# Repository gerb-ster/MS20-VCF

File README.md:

# Korg MS20 VCF

A(nother) eurorack adaptation of this classic Korg VCF from the MS20. 

## Status: Finished

- done: first schematic & board design
- done: breadboard and test
- done: design frontpanel
- done: order PCB and build prototype

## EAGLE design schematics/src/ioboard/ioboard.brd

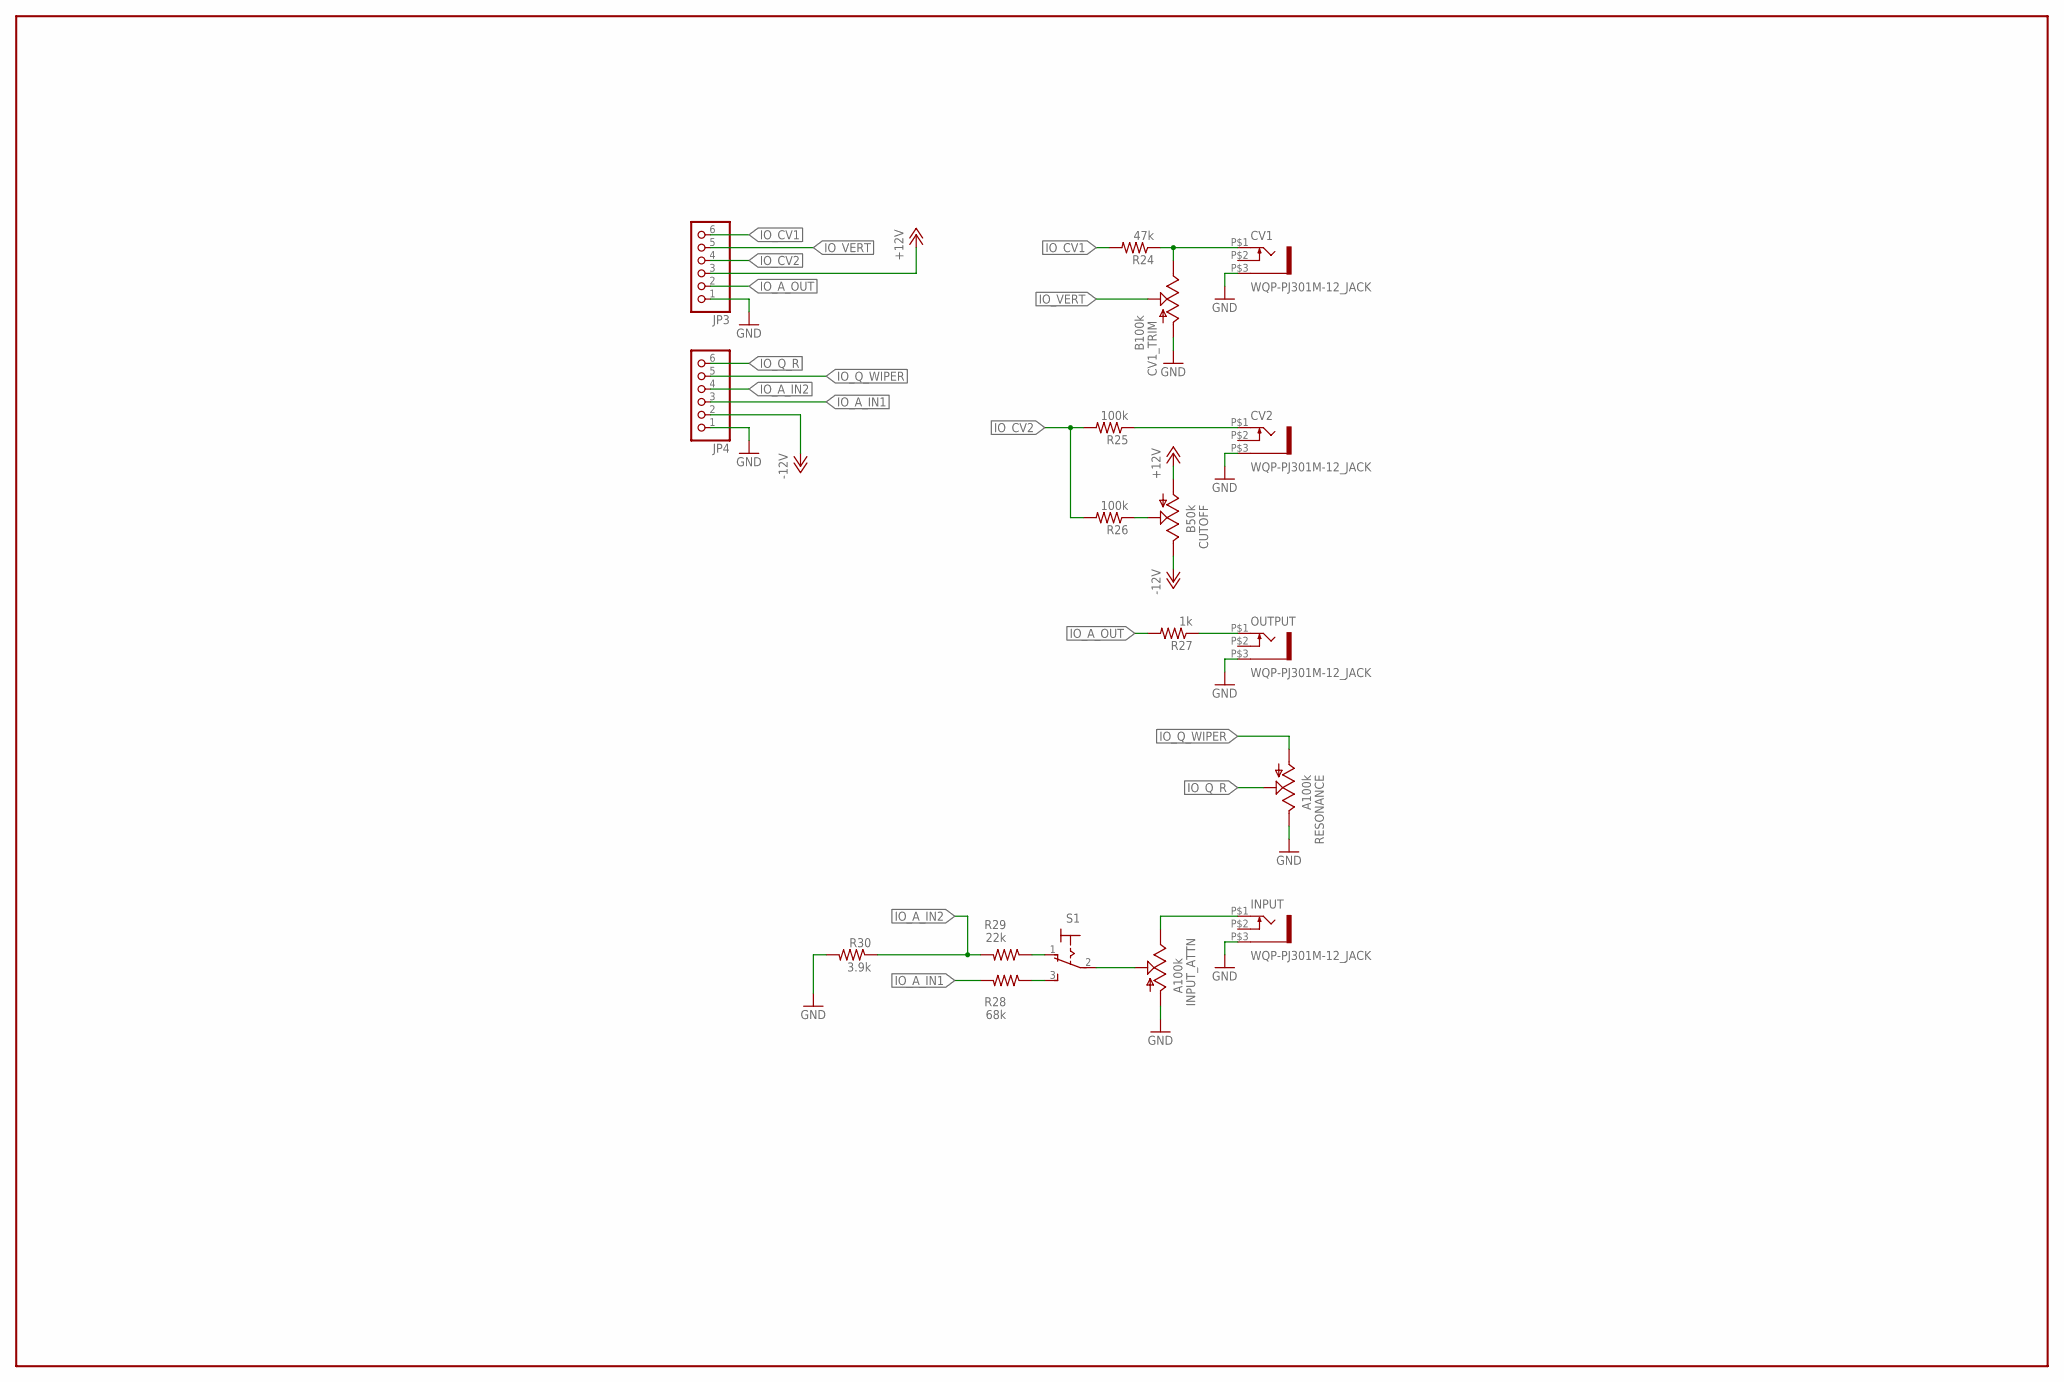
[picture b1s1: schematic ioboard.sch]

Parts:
CUTOFF: B50k; EVUF
CV1, CV2: WQP-PJ301M-12_JACK
CV1_TRIM: B100k; EVUF
INPUT: WQP-PJ301M-12_JACK
INPUT_ATTN: A100k; EVUF
JP3, JP4: PINHD-1X6; 1X06
OUTPUT: WQP-PJ301M-12_JACK
R24: 47k; 0207/7
R25, R26: 100k; 0207/7
R27: 1k; 0207/7
R28: 68k; 0207/7
R29: 22k; 0207/7
R30: 3.9k; 0207/7
RESONANCE: A100k; EVUF
S1: M9040P

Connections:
+12V: CUTOFF.1 (A), JP3.3
-12V: CUTOFF.3 (E), JP4.2
GND: CV1.P$3 (1), CV1_TRIM.1 (A), CV2.P$3 (1), INPUT.P$3 (1), INPUT_ATTN.1 (A), JP3.1, JP4.1, OUTPUT.P$3 (1), R30.2, RESONANCE.3 (E)
IO_A_IN1: JP4.3, R28.2
IO_A_IN2: JP4.4, R29.2, R30.1
IO_A_OUT: JP3.2, R27.2
IO_CV1: JP3.6, R24.2
IO_CV2: JP3.4, R25.2, R26.2
IO_Q_R: JP4.6, RESONANCE.2 (S)
IO_Q_WIPER: JP4.5, RESONANCE.1 (A)
IO_VERT: CV1_TRIM.2 (S), JP3.5
unnamed: CV2.P$1 (2), R25.1
unnamed: INPUT_ATTN.2 (S), S1.2
unnamed: CV1.P$1 (2), CV1_TRIM.3 (E), R24.1
unnamed: OUTPUT.P$1 (2), R27.1
unnamed: CUTOFF.2 (S), R26.1
unnamed: R29.1, S1.1 (O)
unnamed: R28.1, S1.3 (S)
unnamed: INPUT.P$1 (2), INPUT_ATTN.3 (E)

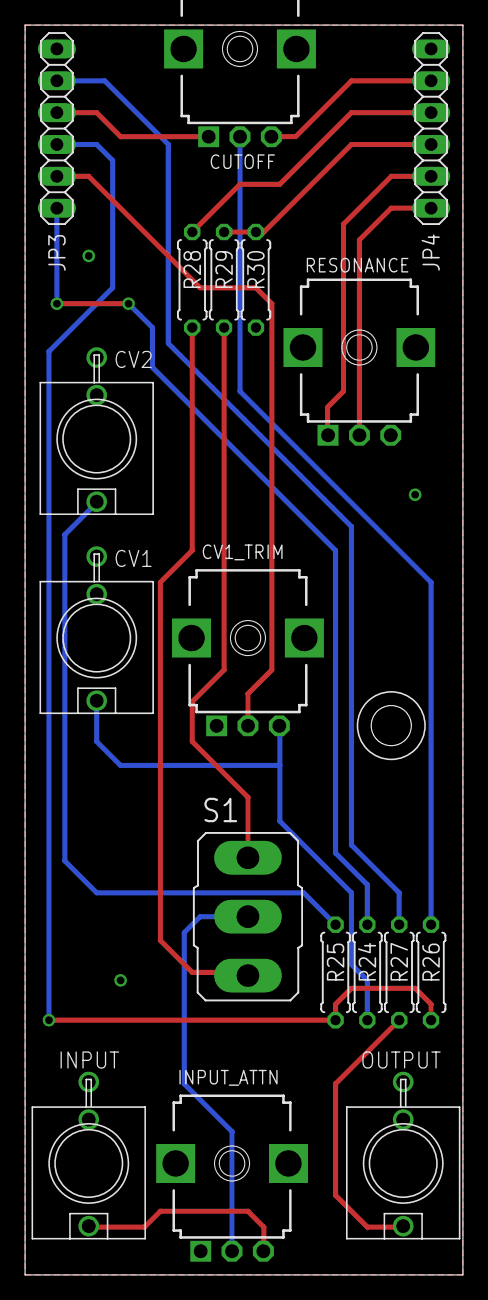
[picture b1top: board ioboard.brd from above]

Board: 2 copper layers, 34.9 x 99.7 mm, 18 parts (0 on the bottom side), 19 nets.

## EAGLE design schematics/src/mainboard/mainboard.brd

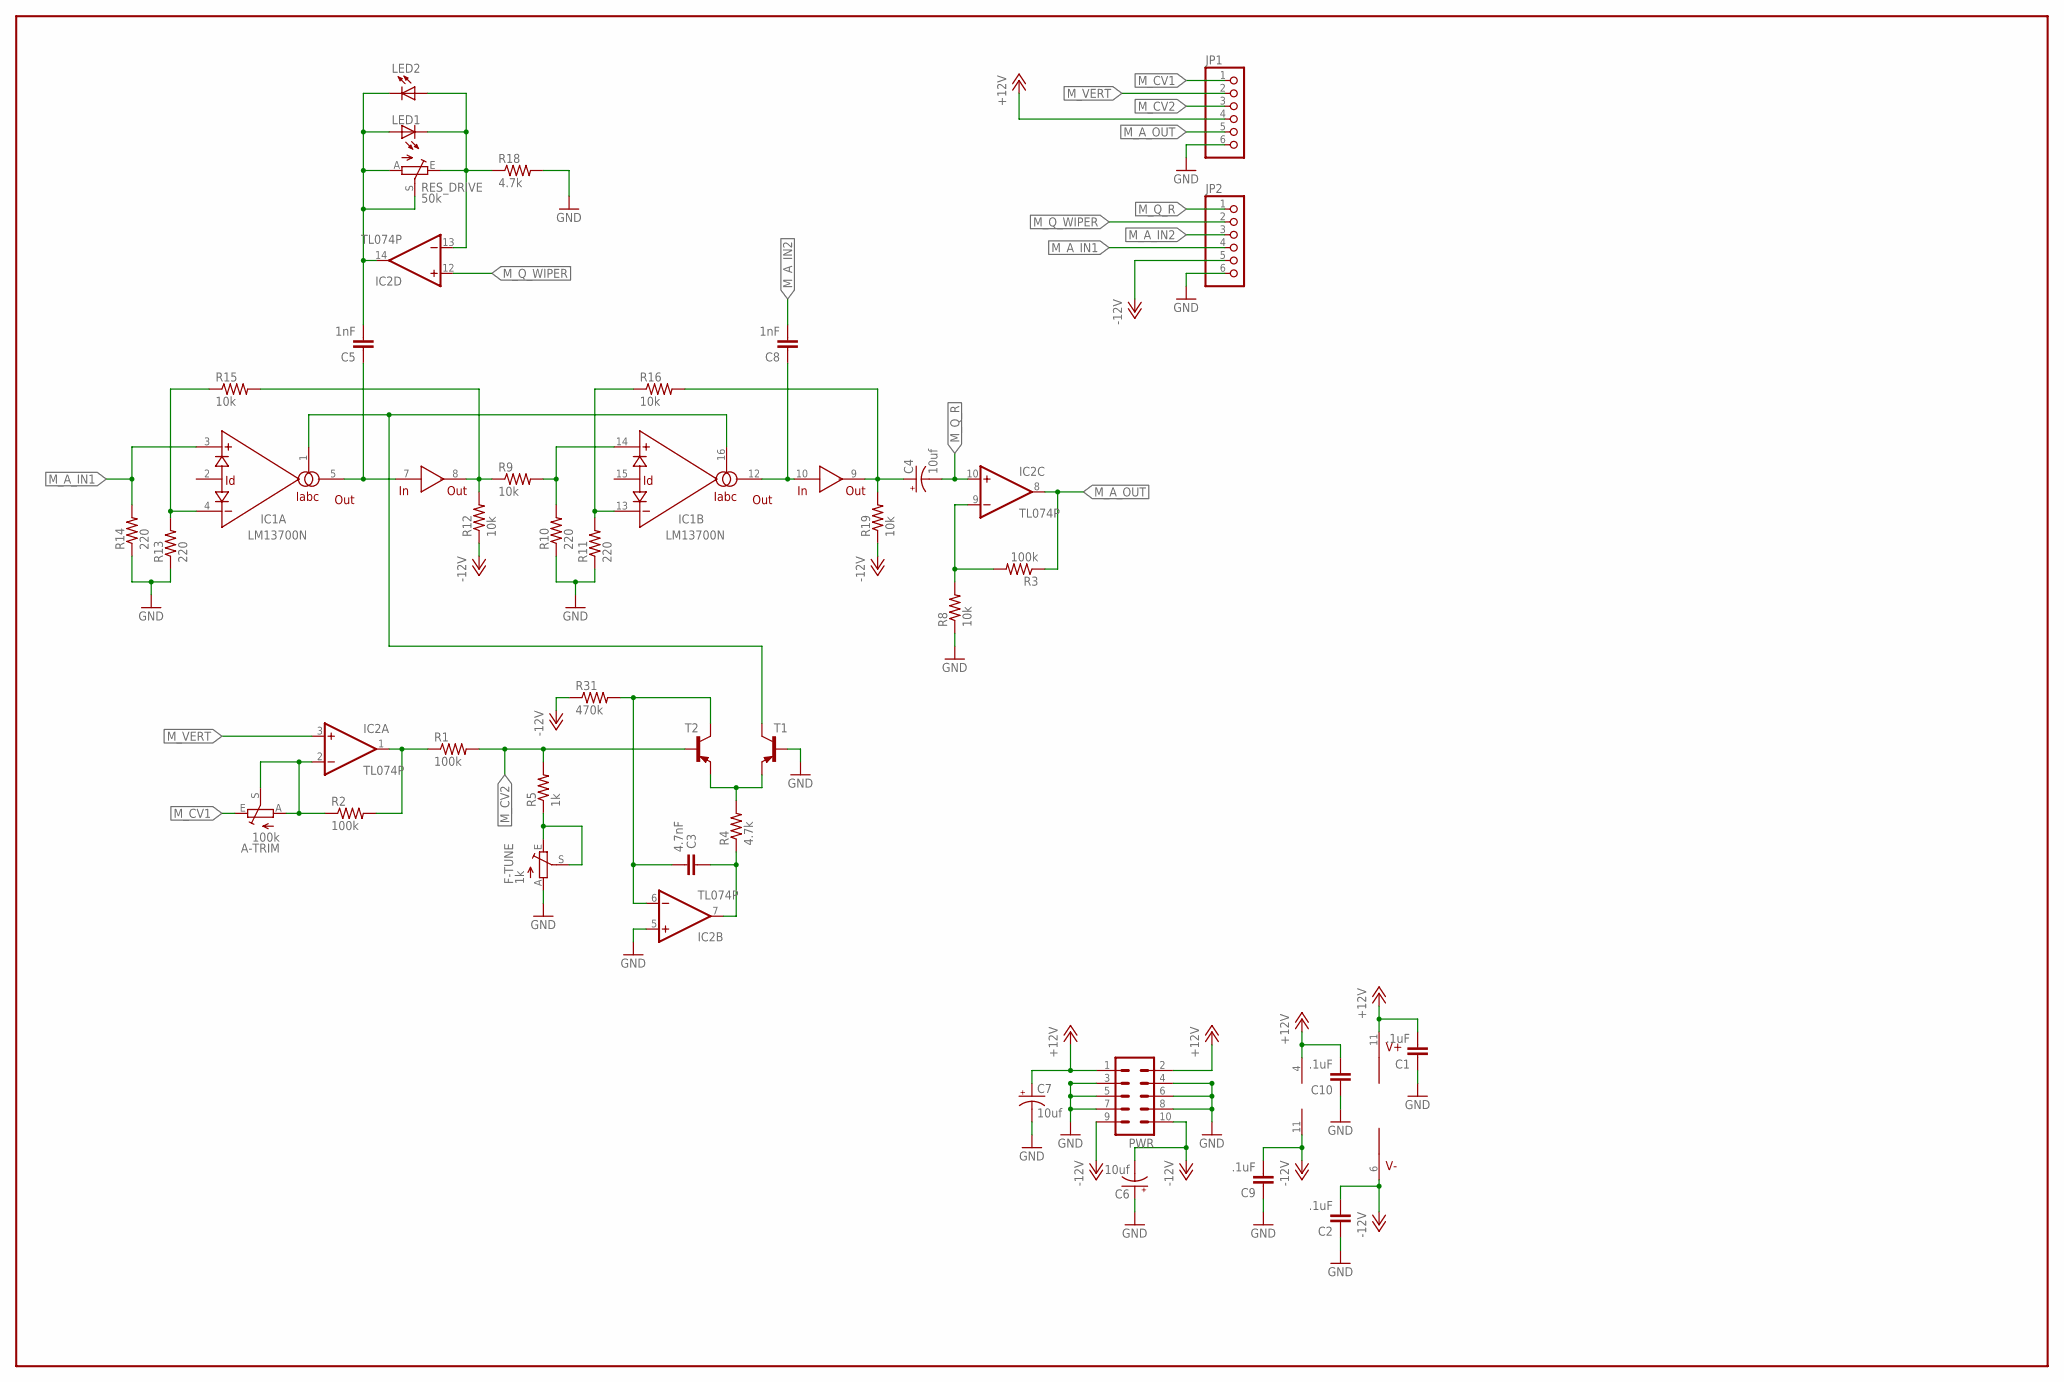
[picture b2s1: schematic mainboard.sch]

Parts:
A-TRIM: 100k; S64YW
C1, C2, C9, C10: .1uF; C050-024X044
C3: 4.7nF; C050-024X044
C4, C6, C7: 10uf; E2,5-5
C5, C8: 1nF; C050-025X075
F-TUNE: 1k; S64YW
IC1: LM13700N; DIL16
IC2: TL074P; DIL14
JP1, JP2: PINHD-1X6; 1X06
LED1, LED2: LED3MM
PWR: ML10
R1, R2, R3: 100k; 0207/7
R4, R18: 4.7k; 0207/7
R5: 1k; 0207/7
R8, R9, R12, R15, R16, R19: 10k; 0207/7
R10, R11, R13, R14: 220; 0207/7
R31: 470k; 0207/7
RES_DRIVE: 50k; S64YW
T1, T2: 2N3906-PNP-TO92-EBC; TO92-EBC

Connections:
+12V: C1.2, C7.+, C10.2, IC1.11 (V+), IC2.4 (V+), JP1.4, PWR.1, PWR.2
-12V: C2.2, C6.-, C9.2, IC1.6 (V-), IC2.11 (V-), JP2.5, PWR.9, PWR.10, R12.1, R19.1, R31.1
GND: C1.1, C2.1, C6.+, C7.-, C9.1, C10.1, F-TUNE.A, IC2.5 (+IN), JP1.6, JP2.6, PWR.3, PWR.4, PWR.5, PWR.6, PWR.7, PWR.8, R8.1, R10.1, R11.1, R13.1, R14.1, R18.2, T1.B
M_A_IN1: IC1.3 (+IN), JP2.4, R14.2
M_A_IN2: C8.2, JP2.3
M_A_OUT: IC2.8 (OUT), JP1.5, R3.1
M_CV1: A-TRIM.E, JP1.1
M_CV2: JP1.3, R1.2, R5.2, T2.B
M_Q_R: C4.-, IC2.10 (+IN), JP2.1
M_Q_WIPER: IC2.12 (+IN), JP2.2
M_VERT: IC2.3 (+IN), JP1.2
unnamed: IC2.1 (OUT), R1.1, R2.2
unnamed: R4.2, T1.E, T2.E
unnamed: A-TRIM.A, A-TRIM.S, IC2.2 (-IN), R2.1
unnamed: C3.1, IC2.7 (OUT), R4.1
unnamed: C5.2, IC2.14 (OUT), LED1.A, LED2.K (C), RES_DRIVE.A, RES_DRIVE.S
unnamed: IC1.4 (-IN), R13.2, R15.1
unnamed: IC1.14 (+IN), R9.2, R10.2
unnamed: IC2.9 (-IN), R3.2, R8.2
unnamed: C8.1, IC1.10 (IN), IC1.12 (OUT)
unnamed: C4.+, IC1.9 (OUT), R16.2, R19.2
unnamed: IC1.13 (-IN), R11.2, R16.1
unnamed: IC2.13 (-IN), LED1.K (C), LED2.A, R18.1, RES_DRIVE.E
unnamed: C5.1, IC1.5 (OUT), IC1.7 (IN)
unnamed: IC1.1 (IABC), IC1.16 (IABC), T1.C
unnamed: F-TUNE.E, F-TUNE.S, R5.1
unnamed: IC1.8 (OUT), R9.1, R12.2, R15.2
unnamed: C3.2, IC2.6 (-IN), R31.2, T2.C

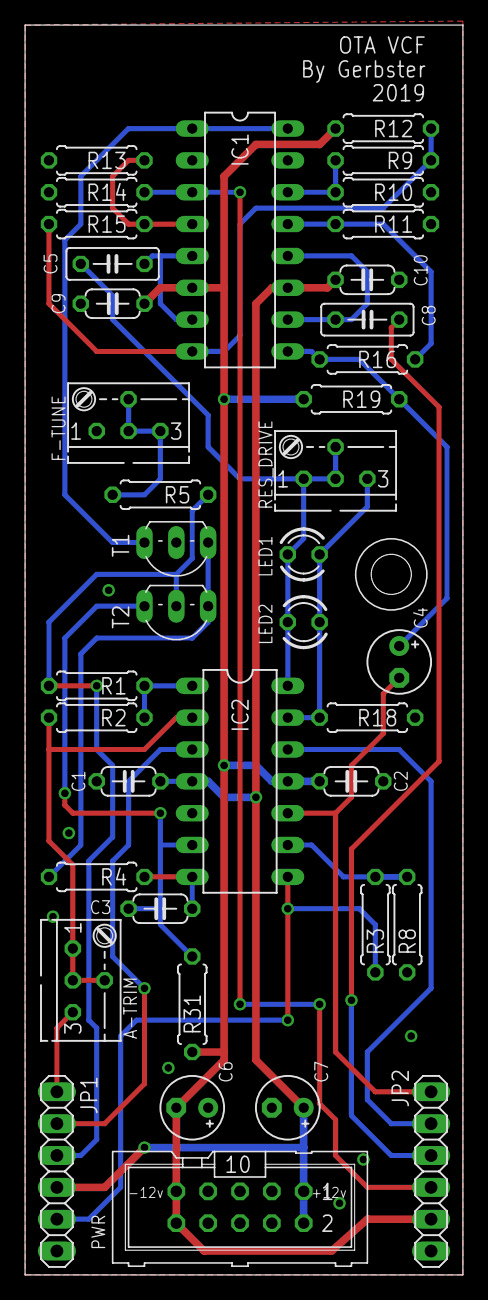
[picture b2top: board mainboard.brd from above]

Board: 2 copper layers, 34.9 x 99.7 mm, 39 parts (0 on the bottom side), 28 nets.

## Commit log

2021-05-10 Added files & structure
2021-05-11 Added Status & Images
2021-08-06 Updated some schematics and docs
2021-08-10 Fixed some bugs and updated documentation
2022-04-20 Some updates & bugfixes
2022-04-22 Fixed schematics & descriptions
2022-05-17 Updated Firmware
2022-05-18 Updated Faceplates
2022-05-18 Fixed issues
2022-05-21 Fixed schematics
2022-05-28 General updates
